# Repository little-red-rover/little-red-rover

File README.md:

# Little Red Rover

The Little Red Rover project has moved! Its new home is the [Little Red Rover GitHub organization](https://github.com/little-red-rover).

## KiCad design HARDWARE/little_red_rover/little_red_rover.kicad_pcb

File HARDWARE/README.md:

# HARDWARE

Little red rover was designed using OnShape and KiCAD (
[OnShape project](https://cad.onshape.com/documents/3c9bcb798eb55dc89c3300c0/w/50990f614f9cfbc3dc016690/e/81981a5257c68cf876fffafa?renderMode=0&uiState=662964f9611b155af71d904d), [KiCAD project](https://github.com/usedhondacivic/little_red_rover/tree/main/HARDWARE/little_red_rover)
).

It is composed of:

* one PCB body
* five 3D printed components (one front skid, two motor mounts, two shims)
* two [TT motors](https://www.adafruit.com/product/3777?gad_source=1&gclid=CjwKCAjw26KxBhBDEiwAu6KXt5uG3_2NXlyCQ1a62bnWJBUqD17JV0xqHqTxL5mOxYhjMxGvXihpPxoCFa0QAvD_BwE)
* two [wheels](https://www.adafruit.com/product/3766?gad_source=1&gclid=CjwKCAjw26KxBhBDEiwAu6KXt0UVN-z849ObhwJ45LRUqls9ojR2lNufE6720qHnvX_B1n_j5iZLehoCHT0QAvD_BwE)
* one [LD20 LiDAR](https://www.youyeetoo.com/products/youyeetoo-fhl-ld20)
* three M3 screws

and thats it!

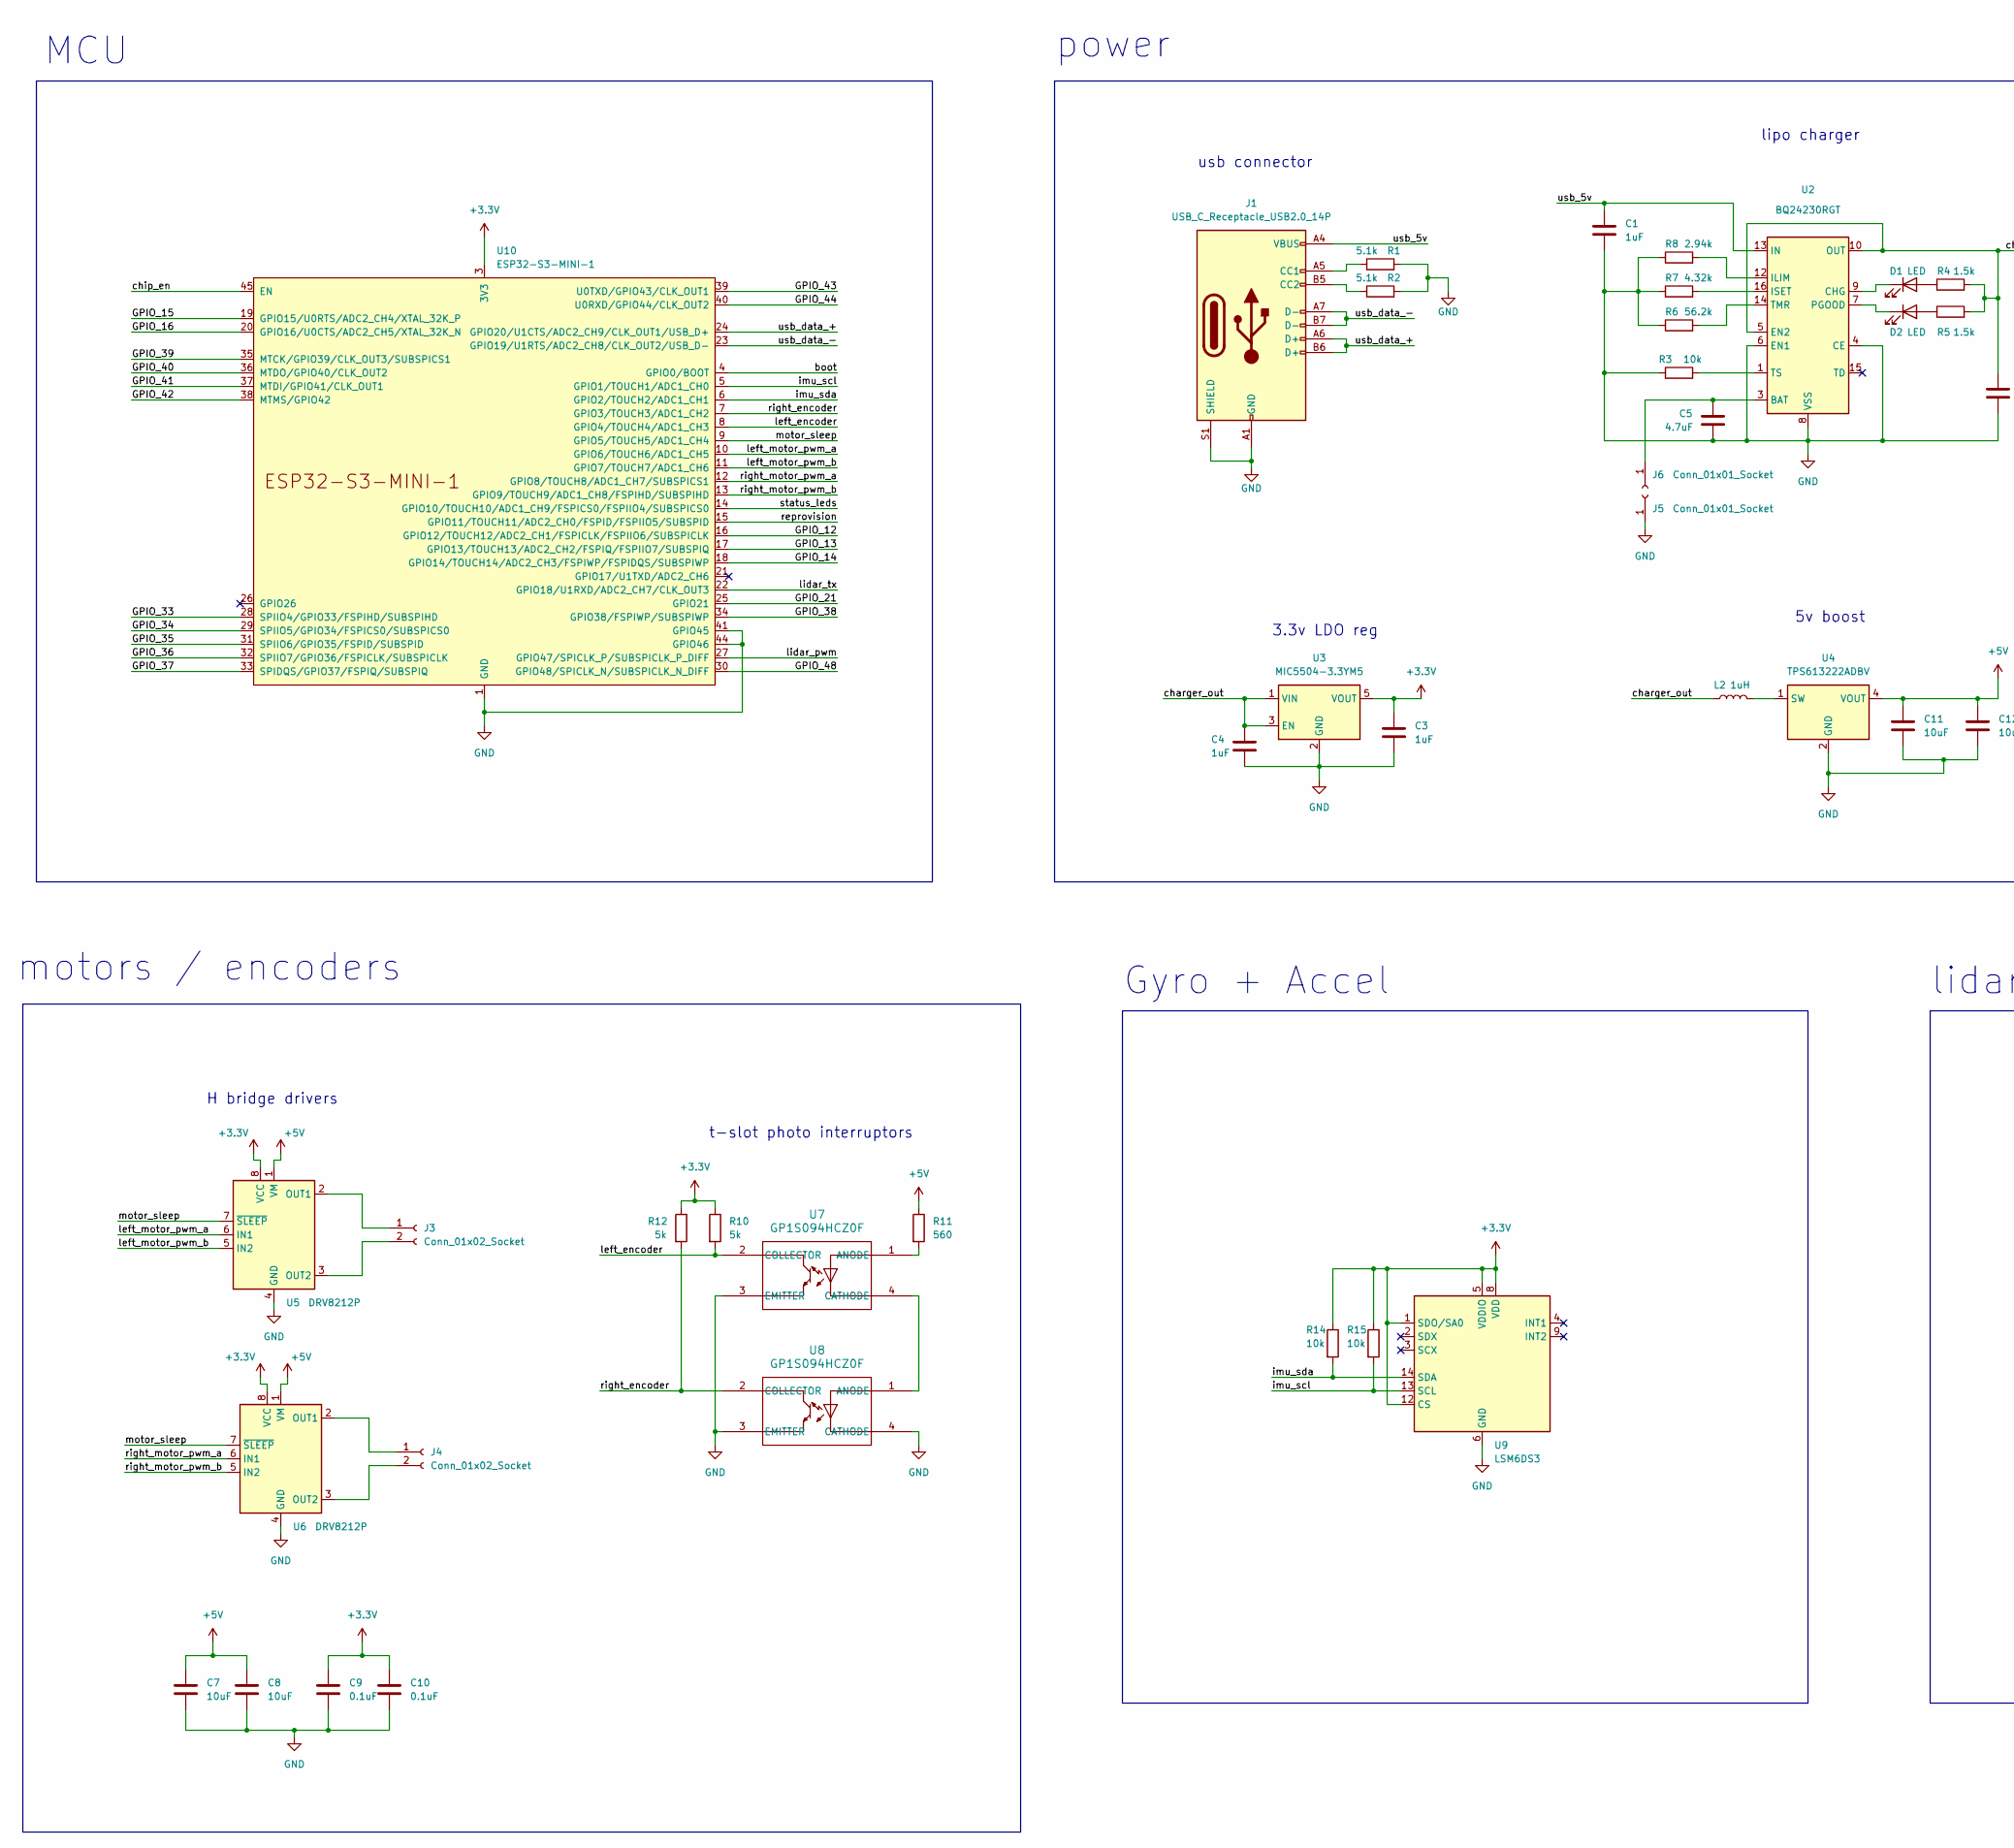
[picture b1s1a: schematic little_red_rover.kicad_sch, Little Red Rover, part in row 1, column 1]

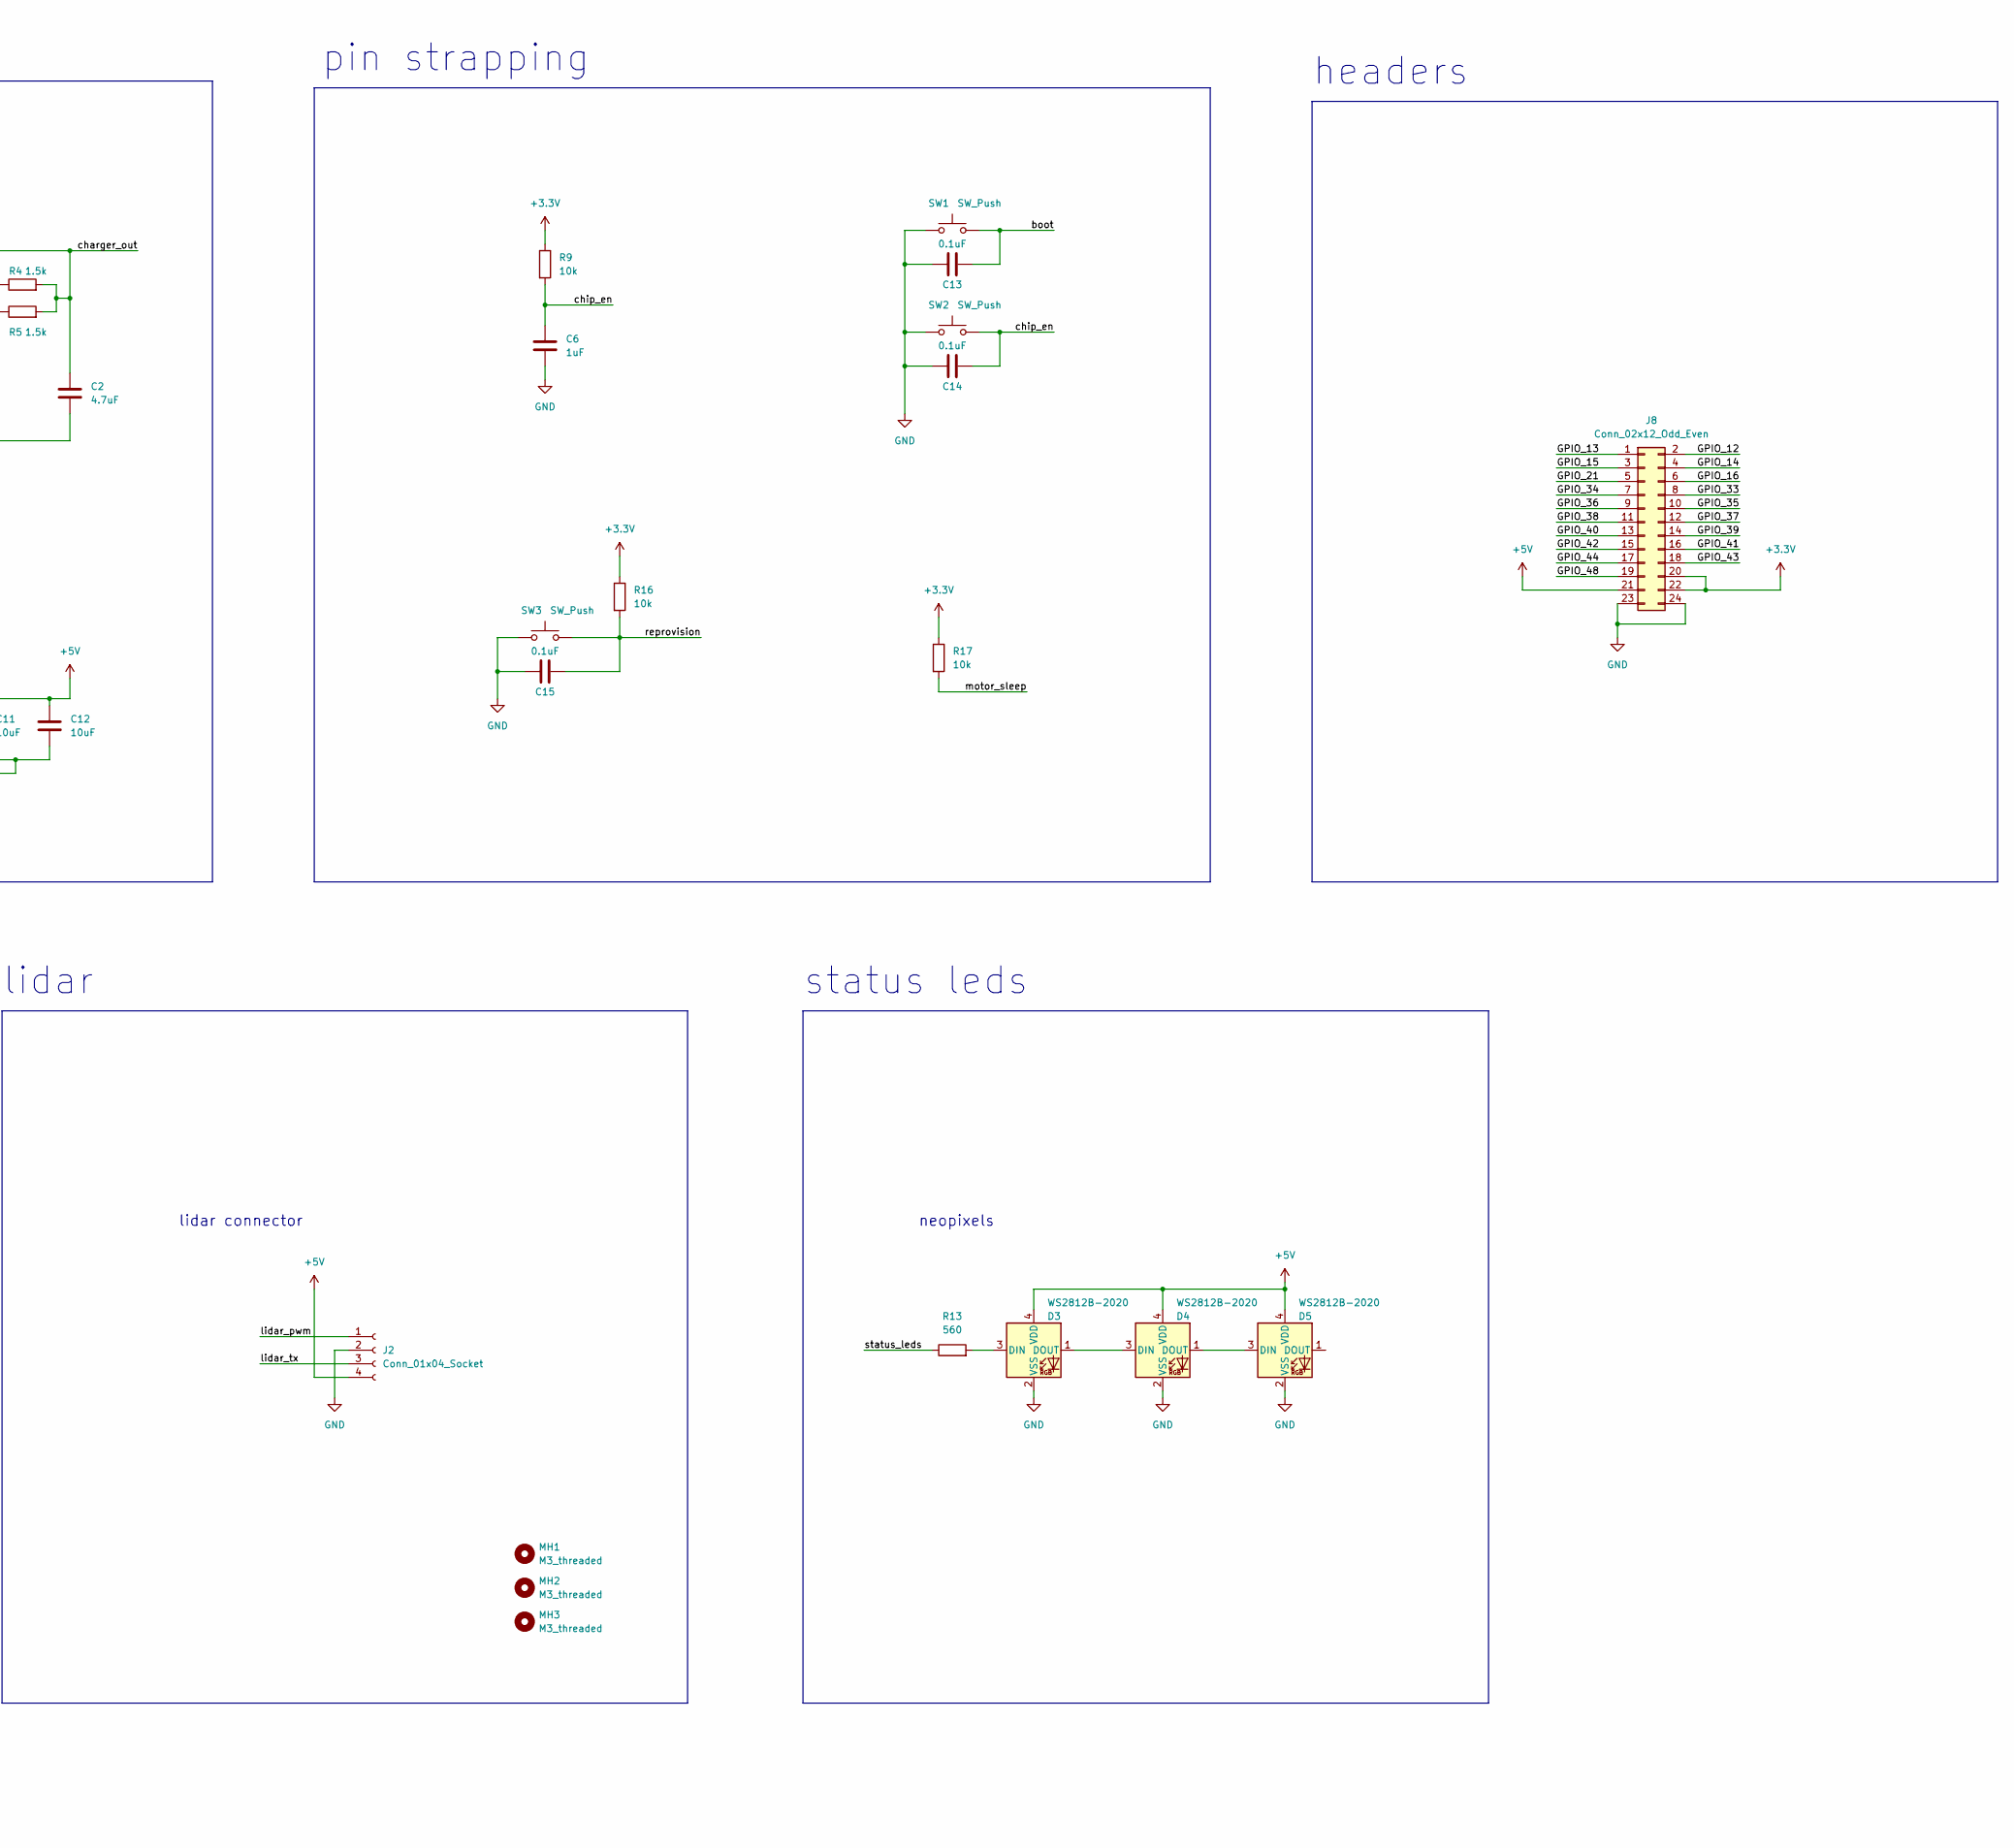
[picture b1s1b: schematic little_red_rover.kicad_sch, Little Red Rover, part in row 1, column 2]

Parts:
C1, C3, C4: 1uF; C_0603_1608Metric_Pad1.08x0.95mm_HandSolder; JLC 0603
C2, C5: 4.7uF; C_0603_1608Metric_Pad1.08x0.95mm_HandSolder; JLC 0603
C6: 1uF; C_0603_1608Metric_Pad1.08x0.95mm_HandSolder
C7, C8, C11, C12: 10uF; C_0603_1608Metric_Pad1.08x0.95mm_HandSolder; JLC 0603
C9, C10: 0.1uF; C_0603_1608Metric_Pad1.08x0.95mm_HandSolder; JLC 0603
C13, C14, C15: 0.1uF; C_0603_1608Metric_Pad1.08x0.95mm_HandSolder
D1, D2: LED; LED_0603_1608Metric_Pad1.05x0.95mm_HandSolder; JLC 0603
D3, D4, D5: WS2812B-2020; LED_WS2812B-2020_PLCC4_2.0x2.0mm; JLC SMD,2x2mm
J1: USB_C_Receptacle_USB2.0_14P; USB_C_Receptacle_GCT_USB4105-xx-A_16P_TopMnt_Horizontal; JLC SMD
J2: Conn_01x04_Socket; CONN_SM04B-GHS-TB_JST; JLC SMD,P=1.25mm
J3, J4: Conn_01x02_Socket; PinSocket_1x02_P2.54mm_Horizontal; JLC Push-Pull,P=2.54mm
J5, J6: Conn_01x01_Socket; 18650_holder; JLC SMD
J8: Conn_02x12_Odd_Even; PinHeader_2x12_P2.54mm_Vertical
L2: 1uH; L_1008_2520Metric_Pad1.43x2.20mm_HandSolder; JLC 1008
MH1, MH2, MH3: M3_threaded; m3_threaded_insert; LCSC C5301780
R1, R2: 5.1k; R_0603_1608Metric_Pad0.98x0.95mm_HandSolder; JLC 0603
R3: 10k; R_0603_1608Metric_Pad0.98x0.95mm_HandSolder; JLC 0603
R4, R5: 1.5k; R_0603_1608Metric_Pad0.98x0.95mm_HandSolder; JLC 0603
R6: 56.2k; R_0603_1608Metric_Pad0.98x0.95mm_HandSolder; JLC 0603
R7: 4.32k; R_0603_1608Metric_Pad0.98x0.95mm_HandSolder; JLC 0603
R8: 2.94k; R_0603_1608Metric_Pad0.98x0.95mm_HandSolder; JLC 0603
R9, R16, R17: 10k; R_0603_1608Metric_Pad0.98x0.95mm_HandSolder
R10, R12: 5k; R_0603_1608Metric_Pad0.98x0.95mm_HandSolder; JLC 0603
R11, R13: 560; R_0603_1608Metric_Pad0.98x0.95mm_HandSolder; JLC 0603
R14, R15: 10k; C_0603_1608Metric_Pad1.08x0.95mm_HandSolder; JLC 0603
SW1, SW2, SW3: SW_Push; SW_Tactile_SPST_NO_Straight_CK_PTS636Sx25SMTRLFS
U2: BQ24230RGT; VQFN-16-1EP_3x3mm_P0.5mm_EP1.68x1.68mm_ThermalVias; JLC VQFN-16-EP(3x3)
U3: MIC5504-3.3YM5; SOT-23-5; JLC SOT-23-5
U4: TPS613222ADBV; SOT-23-5; JLC SOT-23-5
U5, U6: DRV8212P; WSON-8-1EP_2x2mm_P0.5mm_EP0.9x1.6mm_ThermalVias; JLC WSON-8(2x2)
U7, U8: GP1S094HCZ0F; TO_4HCZ0F_SHP; JLC DIP-4
U9: LSM6DS3; LGA-14_3x2.5mm_P0.5mm_LayoutBorder3x4y; JLC LGA-14(2.5x3)
U10: ESP32-S3-MINI-1; ESP32-S2-MINI-1_HandSoldering

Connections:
+3.3V: C3.1, C9.1, C10.1, J8.20, J8.22, R9.1, R10.1, R12.1, R14.1, R15.1, R16.1, R17.1, U3.5 (VOUT), U5.8 (VCC), U6.8 (VCC), U9.1 (SDO/SA0), U9.5 (VDDIO), U9.8 (VDD), U9.12 (CS), U10.3 (3V3)
+5V: C7.1, C8.1, C11.1, C12.1, D3.4 (VDD), D4.4 (VDD), D5.4 (VDD), J2.4, J8.21, R11.1, U4.4 (VOUT), U5.1 (VM), U6.1 (VM)
/GPIO_12: J8.2, U10.16 (GPIO12/TOUCH12/ADC2_CH1/FSPICLK/FSPIIO6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)
/GPIO_13: J8.1, U10.17 (GPIO13/TOUCH13/ADC2_CH2/FSPIQ/FSPIIO7/S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)
/GPIO_14: J8.4, U10.18 (GPIO14/TOUCH14/ADC2_CH3/FSPIWP/FSPIDQS/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)
/GPIO_15: J8.3, U10.19 (GPIO15/U0RTS/ADC2_CH4/XTAL_32K_P)
/GPIO_16: J8.6, U10.20 (GPIO16/U0CTS/ADC2_CH5/XTAL_32K_N)
/GPIO_21: J8.5, U10.25 (GPIO21)
/GPIO_33: J8.8, U10.28 (SPIIO4/GPIO33/FSPIHD/SUBSPIHD)
/GPIO_34: J8.7, U10.29 (SPIIO5/GPIO34/FSPICS0/SUBSPICS0)
/GPIO_35: J8.10, U10.31 (SPIIO6/GPIO35/FSPID/SUBSPID)
/GPIO_36: J8.9, U10.32 (SPIIO7/GPIO36/FSPICLK/SUBSPICLK)
/GPIO_37: J8.12, U10.33 (SPIDQS/GPIO37/FSPIQ/SUBSPIQ)
/GPIO_38: J8.11, U10.34 (GPIO38/FSPIWP/SUBSPIWP)
/GPIO_39: J8.14, U10.35 (MTCK/GPIO39/CLK_OUT3/SUBSPICS1)
/GPIO_40: J8.13, U10.36 (MTDO/GPIO40/CLK_OUT2)
/GPIO_41: J8.16, U10.37 (MTDI/GPIO41/CLK_OUT1)
/GPIO_42: J8.15, U10.38 (MTMS/GPIO42)
/GPIO_43: J8.18, U10.39 (U0TXD/GPIO43/CLK_OUT1)
/GPIO_44: J8.17, U10.40 (U0RXD/GPIO44/CLK_OUT2)
/GPIO_48: J8.19, U10.30 (GPIO48/SPICLK_N/SUBSPICLK_N_DIFF)
/boot: C13.2, SW1.2, U10.4 (GPIO0/BOOT)
/charger_out: C2.1, C4.1, L2.1, R4.2, R5.2, U2.5 (EN2), U2.10 (OUT), U2.11 (OUT), U3.1 (VIN), U3.3 (EN)
/chip_en: C6.1, C14.2, R9.2, SW2.2, U10.45 (EN)
/imu_scl: R15.2, U9.13 (SCL), U10.5 (GPIO1/TOUCH1/ADC1_CH0)
/imu_sda: R14.2, U9.14 (SDA), U10.6 (GPIO2/TOUCH2/ADC1_CH1)
/left_encoder: R10.2, U7.2 (COLLECTOR), U10.8 (GPIO4/TOUCH4/ADC1_CH3)
/left_motor_pwm_a: U5.6 (IN1), U10.10 (GPIO6/TOUCH6/ADC1_CH5)
/left_motor_pwm_b: U5.5 (IN2), U10.11 (GPIO7/TOUCH7/ADC1_CH6)
/lidar_pwm: J2.1, U10.27 (GPIO47/SPICLK_P/SUBSPICLK_P_DIFF)
/lidar_tx: J2.3, U10.22 (GPIO18/U1RXD/ADC2_CH7/CLK_OUT3)
/motor_sleep: R17.2, U5.7 (~SLEEP), U6.7 (~SLEEP), U10.9 (GPIO5/TOUCH5/ADC1_CH4)
/reprovision: C15.2, R16.2, SW3.2, U10.15 (GPIO11/TOUCH11/ADC2_CH0/FSPID/FSPIIO5/S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)
/right_encoder: R12.2, U8.2 (COLLECTOR), U10.7 (GPIO3/TOUCH3/ADC1_CH2)
/right_motor_pwm_a: U6.6 (IN1), U10.12 (GPIO8/TOUCH8/ADC1_CH7/SUBSPICS1)
/right_motor_pwm_b: U6.5 (IN2), U10.13 (GPIO9/TOUCH9/ADC1_CH8/FSPIHD/SUBSPIHD)
/status_leds: R13.1, U10.14 (GPIO10/TOUCH10/ADC1_CH9/FSPICS0/FSPIIO4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)
/usb_5v: C1.1, J1.A4 (VBUS), J1.A9 (VBUS), J1.B4 (VBUS), J1.B9 (VBUS), U2.13 (IN)
/usb_data_+: J1.A6 (D+), J1.B6 (D+), U10.24 (GPIO20/U1CTS/ADC2_CH9/CLK_OUT1/USB_D+)
/usb_data_-: J1.A7 (D-), J1.B7 (D-), U10.23 (GPIO19/U1RTS/ADC2_CH8/CLK_OUT2/USB_D-)
GND: C1.2, C2.2, C3.2, C4.2, C5.2, C6.2, C7.2, C8.2, C9.2, C10.2, C11.2, C12.2, C13.1, C14.1, C15.1, D3.2 (VSS), D4.2 (VSS), D5.2 (VSS), J1.A1 (GND), J1.A12 (GND), J1.B1 (GND), J1.B12 (GND), J1.S1 (SHIELD), J2.2, J5.1, J8.23, J8.24, R1.2, R2.2, R3.1, R6.1, R7.1, R8.1, SW1.1, SW2.1, SW3.1, U2.4 (CE), U2.6 (EN1), U2.8 (VSS), U2.17 (VSS), U3.2 (GND), U4.2 (GND), U5.4 (GND), U5.9 (GND), U6.4 (GND), U6.9 (GND), U7.3 (EMITTER), U8.3 (EMITTER), U8.4 (CATHODE), U9.6 (GND), U9.7 (GND), U10.1 (GND), U10.2 (GND), U10.41 (GPIO45), U10.42 (GND), U10.43 (GND), U10.44 (GPIO46), U10.46 (GND), U10.47 (GND), U10.48 (GND), U10.49 (GND), U10.50 (GND), U10.51 (GND), U10.52 (GND), U10.53 (GND), U10.54 (GND), U10.55 (GND), U10.56 (GND), U10.57 (GND), U10.58 (GND), U10.59 (GND), U10.60 (GND), U10.61 (GND), U10.62 (GND), U10.63 (GND), U10.64 (GND), U10.65 (GND)
unnamed: D1.2 (A), R4.1
unnamed: D1.1 (K), U2.9 (CHG)
unnamed: D2.2 (A), R5.1
unnamed: D2.1 (K), U2.7 (PGOOD)
unnamed: D3.3 (DIN), R13.2
unnamed: D3.1 (DOUT), D4.3 (DIN)
unnamed: D4.1 (DOUT), D5.3 (DIN)
unnamed: J1.A5 (CC1), R1.1
unnamed: J1.B5 (CC2), R2.1
unnamed: J3.1, U5.2 (OUT1)
unnamed: J3.2, U5.3 (OUT2)
unnamed: J4.1, U6.2 (OUT1)
unnamed: J4.2, U6.3 (OUT2)
unnamed: C5.1, J6.1, U2.2 (BAT), U2.3 (BAT)
unnamed: R8.2, U2.12 (ILIM)
unnamed: R7.2, U2.16 (ISET)
unnamed: R6.2, U2.14 (TMR)
unnamed: R3.2, U2.1 (TS)
unnamed: L2.2, U4.1 (SW)
unnamed: R11.2, U7.1 (ANODE)
unnamed: U7.4 (CATHODE), U8.1 (ANODE)

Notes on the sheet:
pin strapping
lidar
3.3v LDO reg
neopixels
lidar connector
H bridge drivers
power
lipo charger
t-slot photo interruptors
usb connector
status leds
headers
MCU
Gyro + Accel
5v boost
motors / encoders

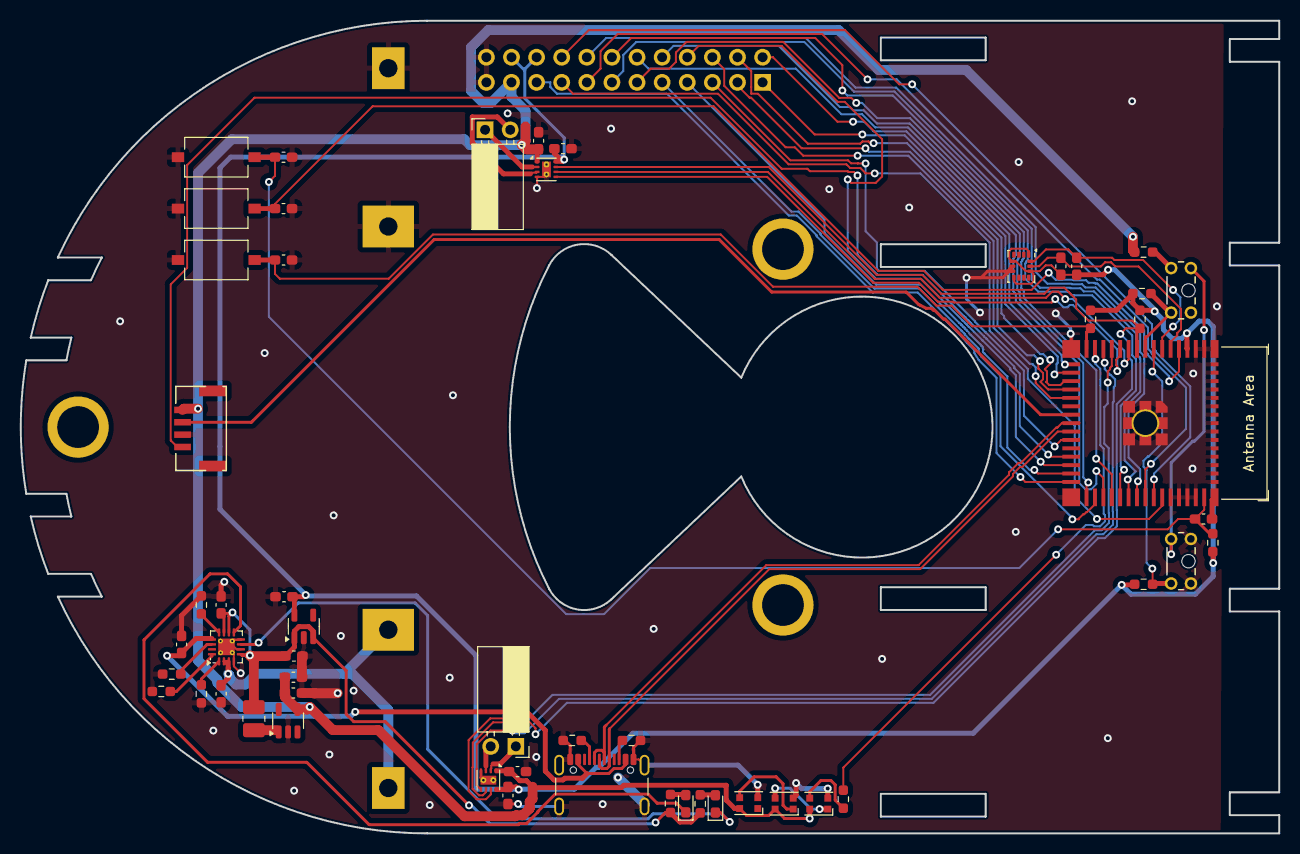
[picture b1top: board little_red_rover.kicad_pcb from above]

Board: 2 copper layers, 127.3 x 82.2 mm, 60 parts (1 on the bottom side), 62 nets.

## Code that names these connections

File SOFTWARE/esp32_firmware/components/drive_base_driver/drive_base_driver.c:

#include "drive_base_driver.h"

#include "esp_log.h"
#include "freertos/FreeRTOS.h"
#include "freertos/idf_additions.h"
#include "freertos/task.h"

#include "esp_timer.h"

#include <stdio.h>
#include <string.h>
#include <time.h>

#include "motor_driver.h"
#include "soc/soc.h"

#include "messages.pb.h"
#include "socket_mgr.h"

#include "status_led_driver.h"

#define DRIVE_BASE_TASK_SIZE (4096)

// PIN DEFINITIONS
#define MOTOR_ENABLE 5

#define LEFT_MOTOR_PWM_A_PIN 7
#define LEFT_MOTOR_PWM_A_CHANNEL 0
#define LEFT_MOTOR_PWM_B_PIN 6
#define LEFT_MOTOR_PWM_B_CHANNEL 1
#define RIGHT_MOTOR_PWM_A_PIN 9
#define RIGHT_MOTOR_PWM_A_CHANNEL 2
#define RIGHT_MOTOR_PWM_B_PIN 8
#define RIGHT_MOTOR_PWM_B_CHANNEL 3

#define LEFT_ENCODER_PIN_A 13
#define LEFT_ENCODER_PIN_B 14
#define RIGHT_ENCODER_PIN_A 3
#define RIGHT_ENCODER_PIN_B 4

// Both in meters
#define WHEEL_DIAMETER 0.060960
#define WHEEL_TRACK 0.13948

#define RCCHECK(fn)                                                            \
    {                                                                          \
        rcl_ret_t temp_rc = fn;                                                \
        if ((temp_rc != RCL_RET_OK)) {                                         \
            printf("Failed status on line %d: %d. Aborting.\n",                \
                   __LINE__,                                                   \
                   (int)temp_rc);                                              \
            vTaskDelete(NULL);                                                 \
        }                                                                      \
    }
#define RCSOFTCHECK(fn)                                                        \
    {                                                                          \
        rcl_ret_t temp_rc = fn;                                                \
        if ((temp_rc != RCL_RET_OK)) {                                         \
            printf("Failed status on line %d: %d. Continuing.\n",              \
                   __LINE__,                                                   \
                   (int)temp_rc);                                              \
        }                                                                      \
    }

static const char *TAG = "drive_base_driver";

// PUBLISHERS
#define PUBLISHER_LOOP_PERIOD_MS 20

// MOTORS
motor_handle_t left_motor_handle;
motor_handle_t right_motor_handle;

UdpPacket wheel_state_msg;

static void set_drive_base_enabled(bool enable)
{
    set_motor_enabled(&left_motor_handle, enable);
    set_motor_enabled(&right_motor_handle, enable);
}

static void set_diff_drive(float left, float right)
{
    set_motor_velocity(&left_motor_handle, left);
    set_motor_velocity(&right_motor_handle, right);
}

void cmd_vel_callback(void *cmd)
{
    TwistCmd twist_cmd = *((TwistCmd *)cmd);
    double v = twist_cmd.v;
    double w = twist_cmd.w;

    // https://control.ros.org/master/doc/ros2_controllers/doc/mobile_robot_kinematics.html#differential-drive-robot
    set_diff_drive((v - ((w * WHEEL_TRACK) / 2.0)) * (2.0 / WHEEL_DIAMETER),
                   (v + ((w * WHEEL_TRACK) / 2.0)) * (2.0 / WHEEL_DIAMETER));
}

void wheel_state_publish_timer_callback()
{
    struct timespec ts;
    clock_gettime(CLOCK_REALTIME, &ts);
    wheel_state_msg.joint_states.time.sec = (int32_t)ts.tv_sec;
    wheel_state_msg.joint_states.time.nanosec = (uint32_t)ts.tv_nsec;

    wheel_state_msg.joint_states.position[0] =
      left_motor_handle.encoder.position;
    wheel_state_msg.joint_states.velocity[0] =
      left_motor_handle.encoder.velocity;
    wheel_state_msg.joint_states.effort[0] =
      (double)left_motor_handle.applied_effort;

    wheel_state_msg.joint_states.position[1] =
      right_motor_handle.encoder.position;
    wheel_state_msg.joint_states.velocity[1] =
      right_motor_handle.encoder.velocity;
    wheel_state_msg.joint_states.effort[1] =
      (double)right_motor_handle.applied_effort;

    if (tx_queue != NULL &&
        xQueueSend(tx_queue, (void *)&wheel_state_msg, 10) != pdTRUE) {
        ESP_LOGE(TAG, "Failed to push scan onto queue");
    }
}

static void drive_base_driver_task(void *arg)
{
    // PWM SETUP
    init_motor_pwm();

    // MOTOR SETUP
    configure_motor(&left_motor_handle,
                    "left_motor",
                    LEFT_MOTOR_PWM_A_PIN,
                    LEFT_MOTOR_PWM_A_CHANNEL,
                    LEFT_MOTOR_PWM_B_PIN,
                    LEFT_MOTOR_PWM_B_CHANNEL,
                    LEFT_ENCODER_PIN_A,
                    LEFT_ENCODER_PIN_B,
                    false);

    configure_motor(&right_motor_handle,
                    "right_motor",
                    RIGHT_MOTOR_PWM_A_PIN,
                    RIGHT_MOTOR_PWM_A_CHANNEL,
                    RIGHT_MOTOR_PWM_B_PIN,
                    RIGHT_MOTOR_PWM_B_CHANNEL,
                    RIGHT_ENCODER_PIN_A,
                    RIGHT_ENCODER_PIN_B,
                    true);

    esp_timer_create_args_t pub_timer_args = {
        .callback = wheel_state_publish_timer_callback,
        .name = "wheel_state_publish_timer"
    };
    esp_timer_handle_t pub_timer_handle;
    ESP_ERROR_CHECK(esp_timer_create(&pub_timer_args, &pub_timer_handle));
    esp_timer_start_periodic(pub_timer_handle, PUBLISHER_LOOP_PERIOD_MS * 1000);

    set_drive_base_enabled(true);

    while (1) {
        vTaskDelay(1000 / portTICK_PERIOD_MS);
    }

    vTaskDelete(NULL);
}

void drive_base_driver_init()
{
    // AGENT SETUP
    register_callback(cmd_vel_callback, eTwistCmd);

    wheel_state_msg.has_joint_states = true;
    wheel_state_msg.joint_states.has_time = true;

    wheel_state_msg.joint_states.name_count = 2;
    wheel_state_msg.joint_states.velocity_count = 2;
    wheel_state_msg.joint_states.position_count = 2;
    wheel_state_msg.joint_states.effort_count = 2;

    strcpy(wheel_state_msg.joint_states.name[0], "wheel_left");
    strcpy(wheel_state_msg.joint_states.name[1], "wheel_right");

    // START TASK
    xTaskCreatePinnedToCore(drive_base_driver_task,
                            "drive_base_driver_task",
                            DRIVE_BASE_TASK_SIZE,
                            NULL,
                            10,
                            NULL,
                            APP_CPU_NUM);
}

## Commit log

2024-02-10 init
2024-02-10 Create LICENSE
2024-02-10 Remove cache
2024-02-10 Add git ignore
2024-02-10 Structures Dockerfiles better and introduces Docker Compose
2024-02-11 MicroROS ping-pong example working
2024-02-13 Implement agent / dev container communication
2024-02-14 Add devcontainer configuration
2024-02-14 Add personal dev env configuration
2024-02-15 Add compile commands for clang support
2024-02-16 Update READMEs
2024-02-16 Fix typos in README
2024-02-17 Move multiple docker files into single, multistaged file
2024-02-17 Remove old docker structure
2024-02-17 Add docker publish action
2024-02-17 Fix docker publish action
2024-02-17 Removing .git folders from docker image
2024-02-18 Move to microROS esp idf component
2024-02-18 Update devcontainer config
2024-02-18 Fix include issue in Dockerfile
2024-02-20 Fix building micro ros agent
2024-02-20 Add softAP wifi provisioning
2024-02-20 Remove signed images
2024-02-26 Add UDP communication
2024-02-27 Reorganize docker, add gazebo + gzweb
2024-02-29 Implements Gazebo + Foxglove sim vis workflow
2024-04-11 Add webserver for provisioning
2024-04-11 Webserver and provisioning working concurently
2024-04-16 Add captive portal for provisioning
2024-04-16 Set softAP name
2024-04-18 Add ip detection script, add automatic uros client reconnect
2024-04-18 Add set agent ip endpoint
2024-04-19 Automagically send agent ip in launchfile
2024-04-19 Add lidar driver
2024-04-19 Add dynamic alloc for publishers
2024-04-20 Fix publisher memory issues
2024-04-20 Working lidar in foxglove
2024-04-21 Initial PCB schematic
2024-04-21 v1.0 board layout
2024-04-24 Update pcb outline, add threaded inserts
2024-04-24 Layout fixes + added QR code
2024-04-24 Update LICENSE
2024-04-24 Add hardware README
2024-04-24 Change 5v boost converter due to shortage
2024-04-25 V1.0 PCB ordered
2024-04-26 Fix threaded inserts not being included in BOM / placement
2024-04-27 Fix hardfault when microcontroller resets while connected to agent
2024-05-02 Add rover urdf
2024-05-02 URDF loading working
2024-05-02 Add frame_id to lidar scan
2024-05-02 Add assets readme
2024-06-03 NAT forwarding for networks with login portals
2024-06-03 Remove robot-ip.txt and references
2024-06-09 Add subscriber tooling, fix issue with new client IP not being respected
2024-06-14 Add drive base driver
2024-06-14 Add initial IMU driver
2024-06-17 Seperate docker / devcontainer files between targets
2024-06-19 Add i2c helpers
2024-06-20 Rewrite i2c functions using new syntax
2024-06-20 Fix github docker publish workflow
2024-06-20 Create build-esp-firmware action
2024-06-20 Rename build-esp-firmware to build-esp-firmware.yml
2024-06-20 Simplify esp idf dockerfile
2024-06-20 Update schematic: use ESP32-S3 mini, unflip usb lines, fix charger CE polarity, add header pins for GPIO, add buttons for strapping pins
2024-06-20 Update PCB layout: Position components for new schematic updates
2024-06-24 Route traces for v1.1
2024-06-25 Add front and back silkscreen
2024-06-25 Init webpage
2024-06-25 Add CNAME
2024-06-25 Create CNAME
2024-06-25 Docs styling
2024-06-26 Docs themeing
2024-06-28 IMU WORKS RAHHHHHH
2024-06-28 Wheel encoders tested
2024-06-28 Remove pull ups on photointerupters
2024-07-01 Streamline launch files
2024-07-01 v1.1 ordered
2024-07-08 Refactor ros2 workspace dockerfile, add black formatter
2024-07-08 Black format existing python files
2024-07-11 Update microros dockerfile
2024-07-11 Remove old micro ros submodule
2024-07-11 Switch to esp32s3
2024-07-11 Fix network bugs that were causing s3 to boot loop
2024-07-11 Add data reading to teleop subscriber
2024-07-11 Tie charger TD low to enable charge termination
2024-07-14 Add encoder driver, teleop working
2024-07-16 Added controller support
2024-07-20 Regenerated urdf from onshape model
2024-07-20 Fix crash related to rapid reconnects to microros agent
2024-07-20 Update robot URDF from onshape
2024-07-20 Invert lidar frame, fix agent disconnect causing a crash
2024-07-22 Move motor driver into seperate file, add PID control
2024-07-22 PID control
2024-07-23 Update schematic: reverse polarity protection, JST motor connectors, power switch
2024-07-23 Update layout: route schematic changes
2024-07-24 Update layout: Correct transistor pin numbers, replace hand solder esp footprint.
2024-07-24 Update layout: Update front silkscreen, adopt semver.
2024-07-25 PCB ordered, v 0.2.0
2024-07-26 Update encoder driver for quadrature
2024-07-27 Update PID weights for quadrature encoders
2024-07-27 Add hysteresis to motor commands
2024-07-28 Change battery IC for a higher current version, change motors to be powered straight from charger output rather than 5v regulation.
2024-07-29 PCB ordered, v 0.2.1
2024-07-29 Fix current limiting for wheel motors
2024-07-30 idiot tax
2024-07-31 Debugging publisher limit
2024-07-31 robot_localization configuration
2024-08-04 Remove pycache files
2024-08-04 Set micro_ros to humble
2024-08-04 app-colcon.meta working
2024-08-04 Move foxglove bridge into ros2_workspace docker image, remove urdf server
2024-08-06 Blocking out getting started writeup
2024-08-06 Adjust for v0.2.1 hardware
2024-08-06 More blocking out of documentation
2024-08-11 Create hardware LICENCE
2024-08-11 Create software LICENSE
2024-08-11 Software, hardware, docs licenses
2024-08-11 Add licenses to README
2024-08-11 Clean up README
2024-08-12 Update robot description for proper wheel directions
2024-08-12 Fixes for agent reconnect
2024-08-12 sdkconfig settings to improve high volume udp throughput with lidar messages
2024-08-12 Add odom_publisher node, fix deserialization bug
2024-08-13 Increase MTU to prevent deserialization errors
2024-08-13 Add .rgignore to get rid of search results from micro_ros_esp_idf_component
2024-08-13 Idiot tax: I can't count
2024-08-13 Update dev container, add type annotation to odom_publisher
2024-08-13 Serialization is working again and I have no idea why
2024-08-13 Working well again, again not sure why
2024-08-14 Bug fixes
2024-08-15 Add socket manager
2024-08-15 Add hal node
2024-08-15 Add msgpack espidf module
2024-08-15 Add nanopb
2024-08-15 Add protocol buffers to ros side, ros2 -> esp TwistCmd publishing working
2024-08-16 RX callbacks working
2024-08-16 Lidar send / recieve working
2024-08-16 Increase network buffer sizes
2024-08-16 Laser, wheel states, cmd_vel over sockets implemented
2024-08-16 Update readme to show that micro-ros has been removed
2024-08-16 Wheel encoder only localization working
2024-08-19 Batch laser messages into single packet for better network performance
2024-08-19 Add slam toolbox + configuration files
2024-08-19 Slam working, needs tuning
2024-08-25 Ordered PCB v0.2.2: FA '24 beta test
2024-08-25 Update URDF to match CAD
2024-08-25 Add status led driver
2024-08-25 Ignore espidf managed components
2024-08-25 Rename little_red_rover_ws to ros2_ws
